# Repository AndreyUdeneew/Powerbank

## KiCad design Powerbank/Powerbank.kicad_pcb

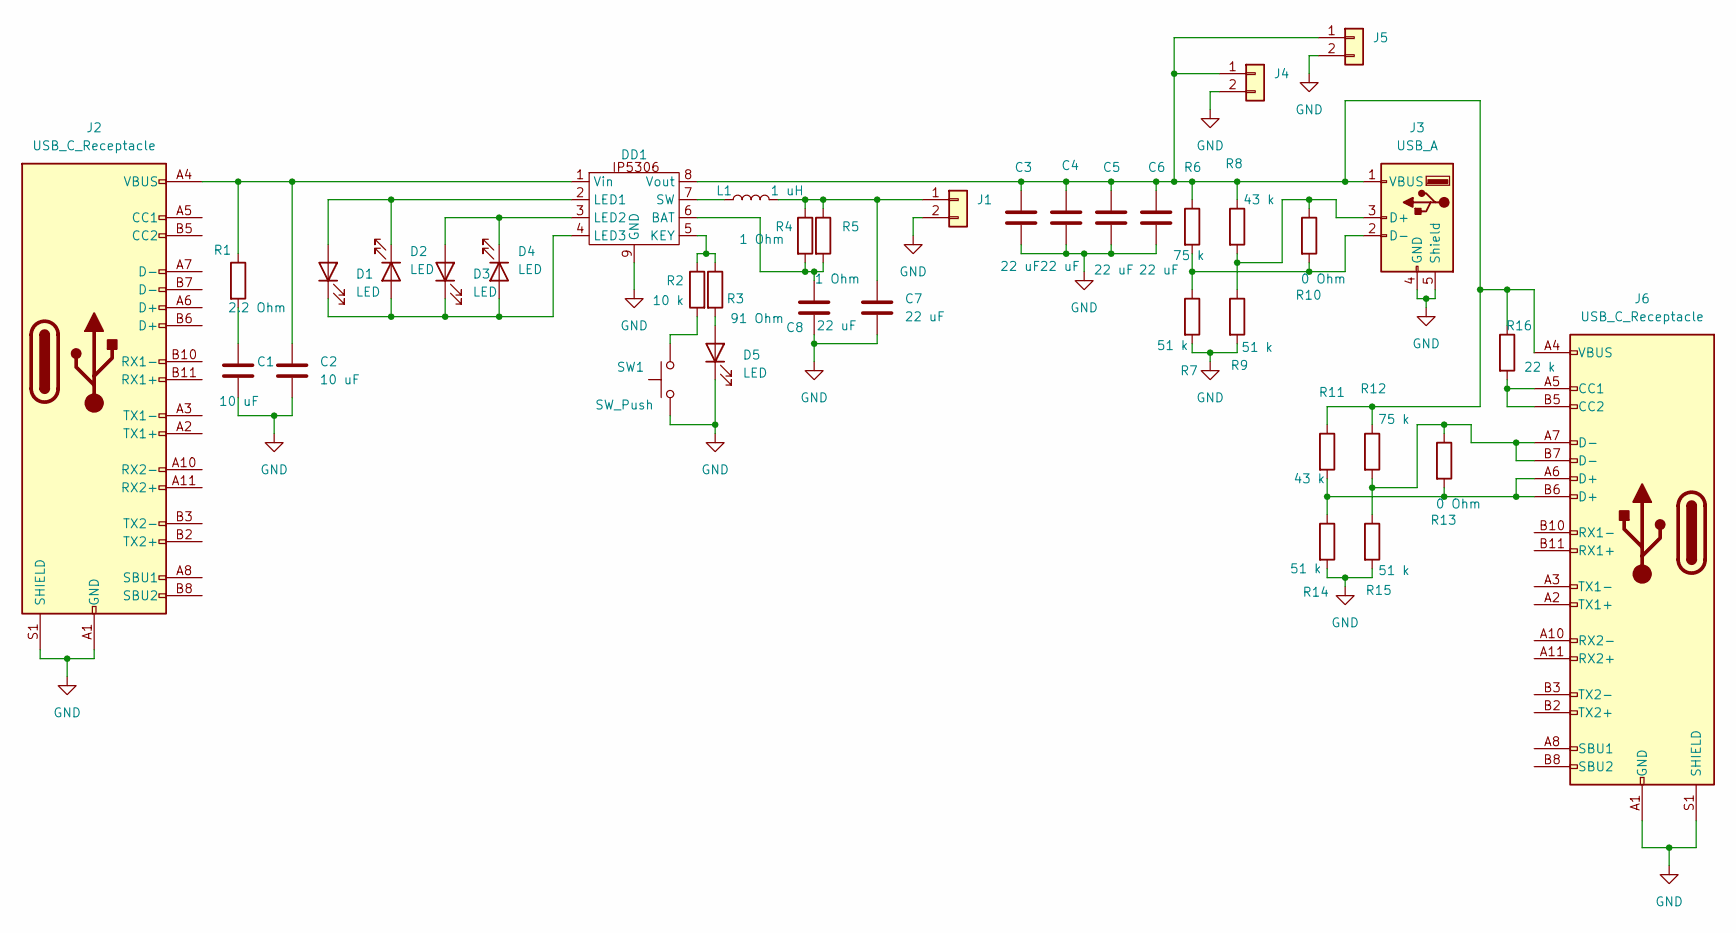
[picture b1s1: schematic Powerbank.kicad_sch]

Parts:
C1, C2: 10 uF; C_1206_3216Metric_Pad1.33x1.80mm_HandSolder
C3, C4, C5, C6, C7, C8: 22 uF; C_1206_3216Metric_Pad1.33x1.80mm_HandSolder
D1, D2, D3, D4: LED; LED_0603_1608Metric_Pad1.05x0.95mm_HandSolder
D5: LED; LED_D5.0mm
DD1: SOIC-8-1EP_3.9x4.9mm_P1.27mm_EP2.95x4.9mm_Mask2.71x3.4mm_Th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
J1, J4, J5: Conn_01x02; JST_XH_B2B-XH-A_1x02_P2.50mm_Vertical
J2, J6: USB_C_Receptacle; USB_C_Receptacle_JAE_DX07S024WJ3R400
J3: USB_A; USB_A_CONNFLY_DS1095-WNR0
L1: 1 uH; L_6.3x6.3_H3
R1: 2.2 Ohm; R_0603_1608Metric_Pad0.98x0.95mm_HandSolder
R2: 10 k; R_0603_1608Metric_Pad0.98x0.95mm_HandSolder
R3: 91 Ohm; R_0603_1608Metric_Pad0.98x0.95mm_HandSolder
R4, R5: 1 Ohm; R_0603_1608Metric_Pad0.98x0.95mm_HandSolder
R6, R12: 75 k; R_0603_1608Metric_Pad0.98x0.95mm_HandSolder
R7, R9, R14, R15: 51 k; R_0603_1608Metric_Pad0.98x0.95mm_HandSolder
R8, R11: 43 k; R_0603_1608Metric_Pad0.98x0.95mm_HandSolder
R10, R13: 0 Ohm; R_0603_1608Metric_Pad0.98x0.95mm_HandSolder
R16: 22 k; R_0603_1608Metric_Pad0.98x0.95mm_HandSolder
SW1: SW_Push; SW_PUSH_6mm_H13mm

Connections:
GND: C1.2, C2.2, C3.2, C4.2, C5.2, C6.2, C7.2, C8.2, D5.1 (K), DD1.9 (GND), J1.2, J2.A1 (GND), J2.A12 (GND), J2.B1 (GND), J2.B12 (GND), J2.S1 (SHIELD), J3.4 (GND), J3.5 (Shield), J4.2, J5.2, J6.A1 (GND), J6.A12 (GND), J6.B1 (GND), J6.B12 (GND), J6.S1 (SHIELD), R7.2, R9.2, R14.2, R15.2, SW1.1
unnamed: C1.1, R1.2
unnamed: D1.2 (A), D2.1 (K), DD1.2 (LED1)
unnamed: D1.1 (K), D2.2 (A), D3.1 (K), D4.2 (A), DD1.4 (LED3)
unnamed: D3.2 (A), D4.1 (K), DD1.3 (LED2)
unnamed: D5.2 (A), R3.2
unnamed: C8.1, DD1.6 (BAT), R4.2, R5.2
unnamed: DD1.5 (KEY), R2.1, R3.1
unnamed: DD1.7 (SW), L1.1
unnamed: C2.1, DD1.1 (Vin), J2.A4 (VBUS), J2.A9 (VBUS), J2.B4 (VBUS), J2.B9 (VBUS), R1.1
unnamed: C3.1, C4.1, C5.1, C6.1, DD1.8 (Vout), J3.1 (VBUS), J4.1, J5.1, J6.A4 (VBUS), J6.A9 (VBUS), J6.B4 (VBUS), J6.B9 (VBUS), R6.1, R8.1, R11.1, R12.1, R16.1
unnamed: C7.1, J1.1, L1.2, R4.1, R5.1
unnamed: J3.3 (D+), R8.2, R9.1, R10.1
unnamed: J3.2 (D-), R6.2, R7.1, R10.2
unnamed: J6.A5 (CC1), J6.B5 (CC2), R16.2
unnamed: J6.A6 (D+), J6.B6 (D+), R11.2, R13.2, R14.1
unnamed: J6.A7 (D-), J6.B7 (D-), R12.2, R13.1, R15.1
unnamed: R2.2, SW1.2

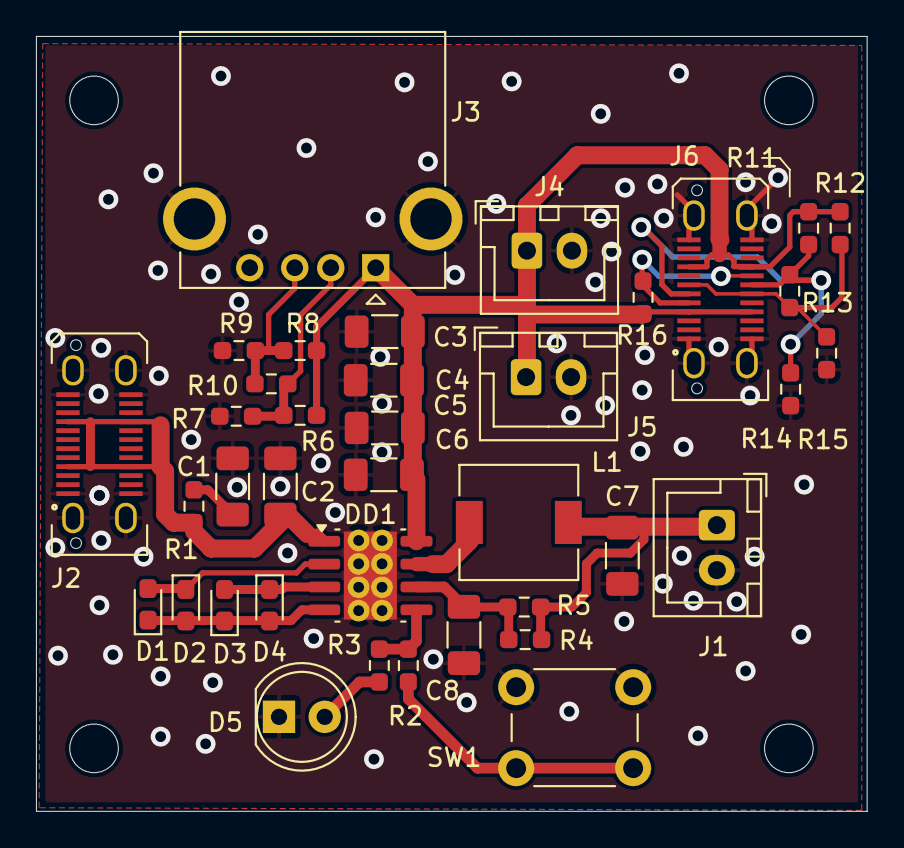
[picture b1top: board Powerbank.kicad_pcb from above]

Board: 2 copper layers, 46.1 x 43.0 mm, 38 parts (0 on the bottom side), 18 nets.

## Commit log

2024-12-30 v0.1 files 4 ordering were added
